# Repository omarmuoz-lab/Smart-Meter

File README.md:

# Smart Meter – Firmware & PCB Designs

This repository contains all the resources for a custom-built **Smart Meter**, including:

- **Firmware** for the embedded microcontroller.
- **PCB designs** for the hardware implementation.

The project is aimed at real-time measurement of electrical parameters such as voltage, current, active power, reactive power, apparent power, power factor, and energy consumption.

---

## 📂 Repository Structure

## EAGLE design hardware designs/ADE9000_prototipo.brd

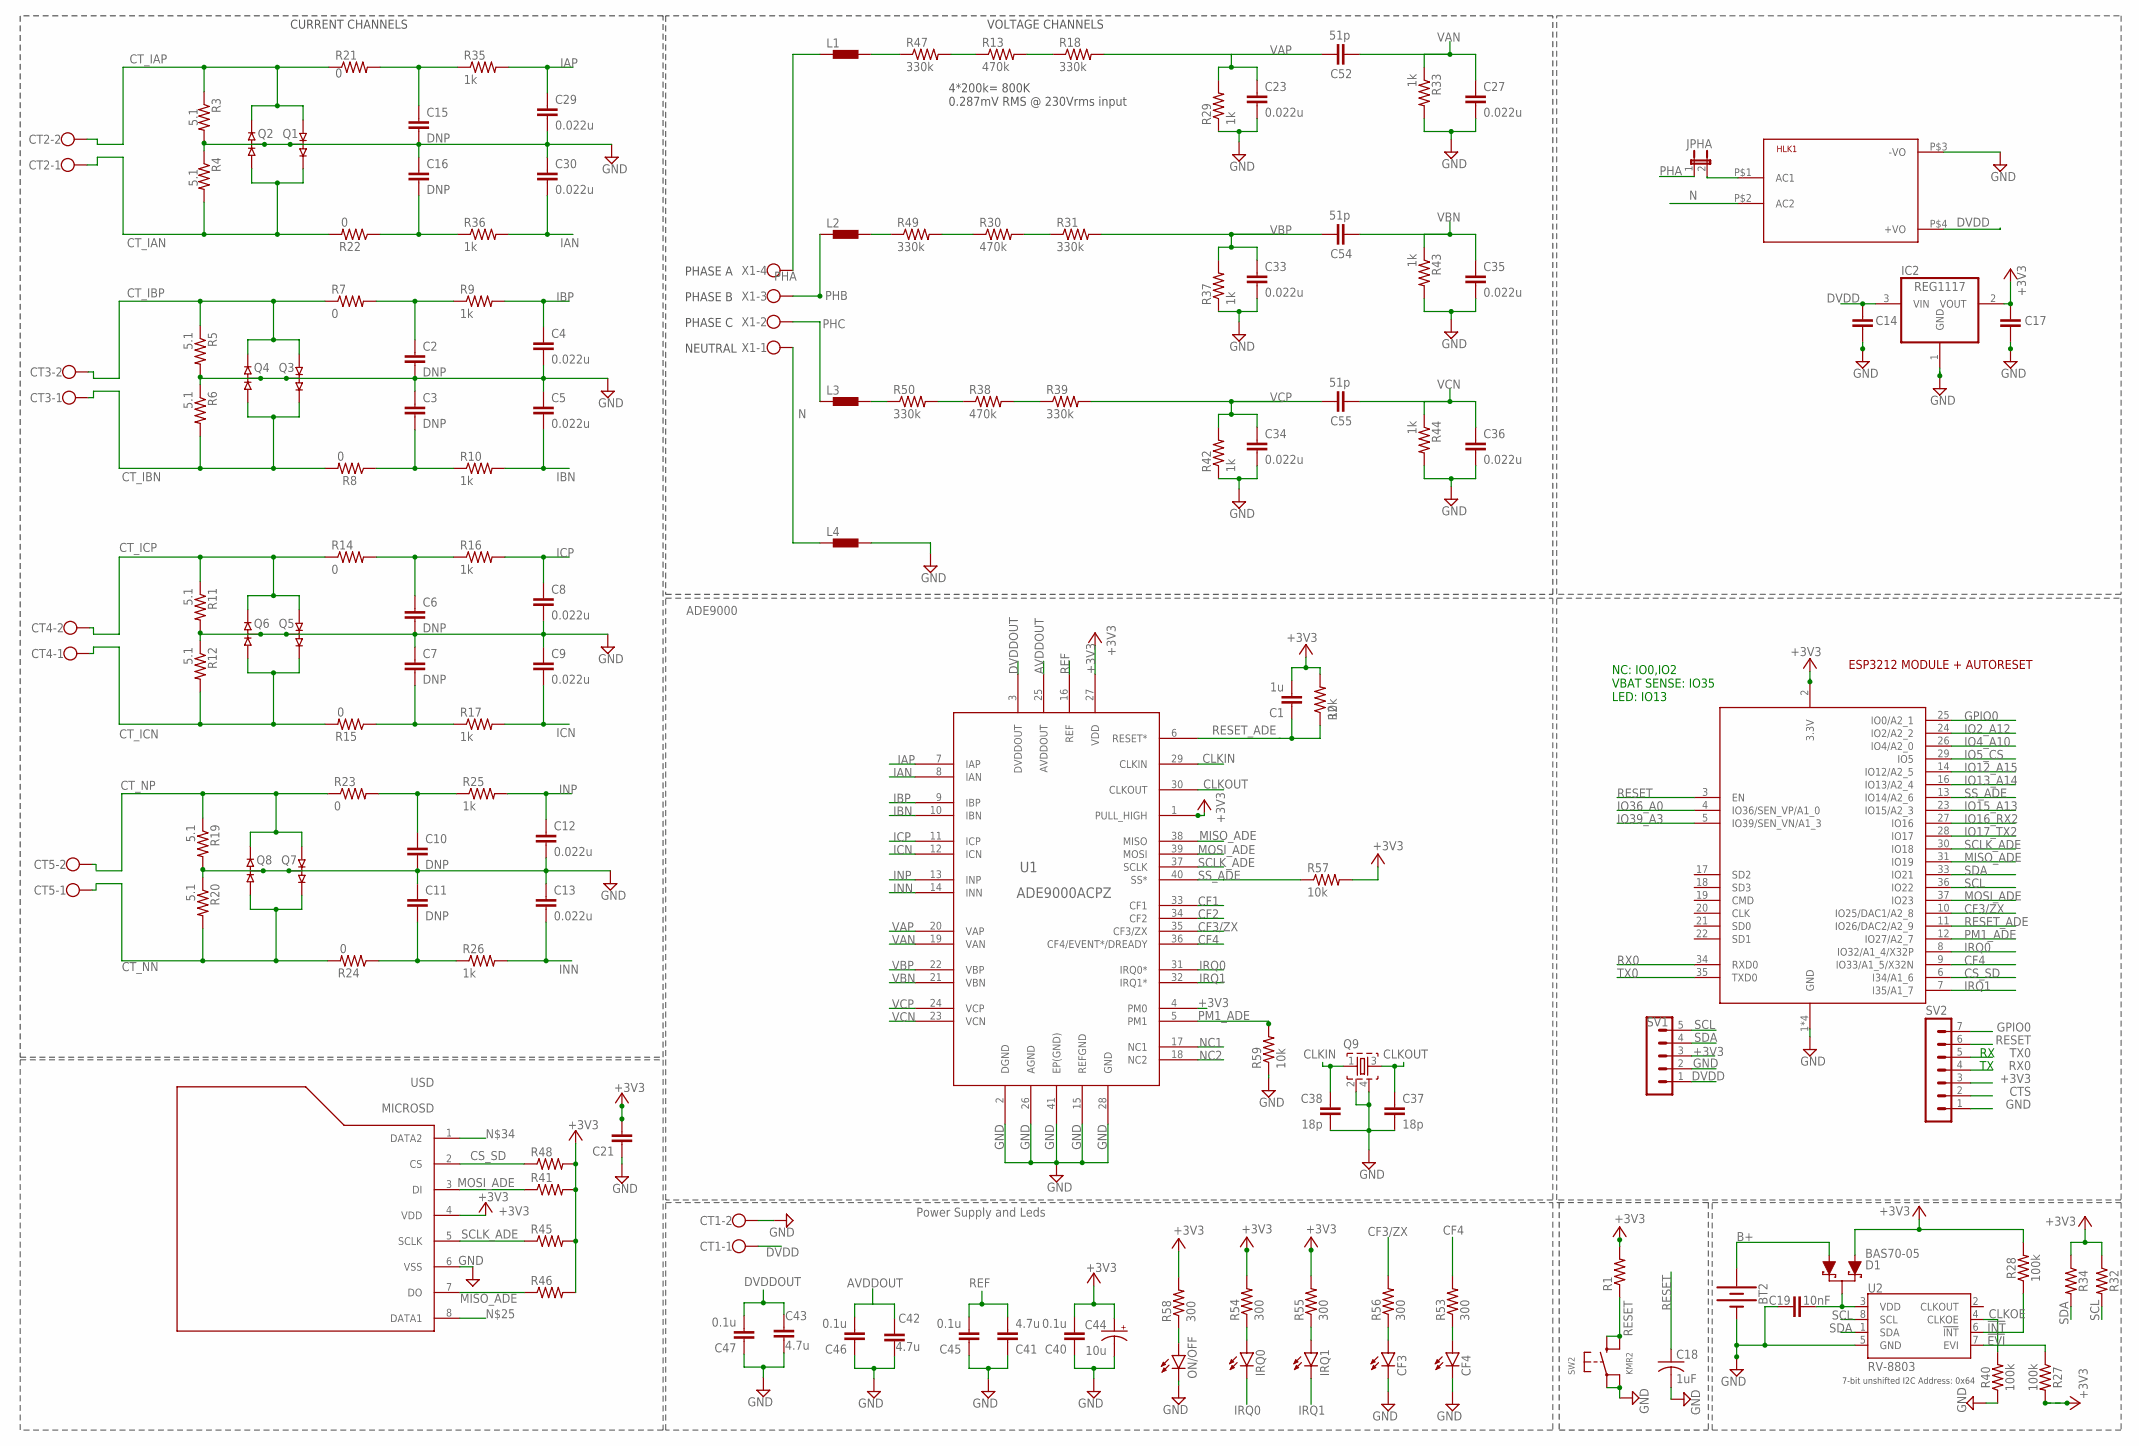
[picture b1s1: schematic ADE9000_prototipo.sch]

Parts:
BT2: BATTERY-12MM_SMD; BATTCON_12MM
C1: 1u; C0805
C2, C3, C6, C7, C10, C11, C15, C16: DNP; C0805
C4, C5, C8, C9, C12, C13, C23, C29, C30, C33, C34: 0.022u; C0805
C14, C17: C-EUC1206; C1206
C18: 1uF; C0805
C19: 10nF; 0603
C21, C40, C45, C46, C47: 0.1u; C0805
C27, C35, C36: 0.022u; C0603
C37, C38: 18p; C0805
C41, C42, C43: 4.7u; C0805
C44: 10u; E1,8-4
C52, C54, C55: 51p; C0603
CF3, CF4: LEDCHIPLED_1206; CHIPLED_1206
CT1, CT2, CT3, CT4, CT5: W237-102
D1: BAS70-05; SOT23-3
HLK1: HLK-PM013W; HLK-PM01
IC2: REG1117; SOT223
IRQ0, IRQ1: LEDCHIPLED_1206; CHIPLED_1206
JPHA: JP1E; JP1
L1, L2, L3, L4: 1500; M0805; DIGIKEY 490-1048-1-ND
ON/OFF: LEDCHIPLED_1206; CHIPLED_1206
Q1, Q2, Q3, Q4, Q5, Q6, Q7, Q8: MMBD4148SE; SOT23-3; DIGIKEY MMBD4148SECT-ND
Q9: ECS-245.7-12-33Q-JES-TR; SMD_4PIN_3.2X2.1; DIGIKEY XC2178CT-ND
R1, R41, R45, R46, R48: R-US_R0805; R0805
R2, R57, R59: 10k; R0805
R3, R5, R11, R19: 5.1; R0805; MFR_PART_NO_# CPF0805B5R1E1
R4, R6, R12, R20: 5.1; R0805
R7, R8, R14, R15, R21, R22, R23, R24: 0; R0805
R9, R10, R16, R17, R25, R26, R29, R35, R36, R37, R42: 1k; R0805
R13, R30, R38: 470k; R0805
R18, R31, R39, R47, R49, R50: 330k; R0805
R27, R28, R40: 100k; 0603
R32: 4.7k; 0603
R33, R43, R44: 1k; R0603
R34: 4.7KOHM-0603-1/10W-1%; 0603
R53, R54, R55, R56, R58: 300; R0805
SV1: MA05-1
SV2: MA07-1
SW2: KMR2; BTN_KMR2_4.6X2.8
U1: ADE9000ACPZ; CP_40_7; DIGIKEY ADE9000ACPZ-RLCT-ND
U2: RV-8803; RV-3028
USD: MICROSD
X1: W237-4
X4: ESP32_WROOM32_SKINNY; WROOM32_SKINNY

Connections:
!EVI: R27.1, U2.7 (EVI)
!INT: R28.1, U2.6 (!INT)
+3V3: C1.2, C17.1, C21.2, C40.2, C44.+, D1.1 (A), IC2.2 (VOUT), R1.2, R2.2, R27.2, R28.2, R32.1, R34.1, R41.2, R45.2, R46.2, R48.2, R54.2, R55.2, R57.2, R58.2, SV1.3, SV2.3, U1.1 (PULL_HIGH), U1.4 (PM0), U1.27 (VDD), USD.4 (VDD), X4.2 (3.3V)
AVDDOUT: C42.1, C46.2, U1.25 (AVDDOUT)
B+: BT2.PWR@1 (+), D1.2 (A1)
CF1: U1.33 (CF1)
CF2: U1.34 (CF2)
CF3/ZX: R56.2, U1.35 (CF3/ZX), X4.10 (IO25/DAC1/A2_8)
CF4: R53.2, U1.36 (CF4/EVENT*/DREADY), X4.9 (IO33/A1_5/X32N)
CLKIN: C38.1, Q9.1, U1.29 (CLKIN)
CLKOE: R40.2, U2.4 (CLKOE)
CLKOUT: C37.1, Q9.3, U1.30 (CLKOUT)
CS_SD: R48.1, USD.2 (CS), X4.6 (I34/A1_6)
CTS: SV2.2
CT_IAN: CT2.1, Q1.2, Q2.1, R4.2, R22.2
CT_IAP: CT2.2, Q1.1, Q2.2, R3.1, R21.1
CT_IBN: CT3.1, Q3.2, Q4.1, R6.2, R8.2
CT_IBP: CT3.2, Q3.1, Q4.2, R5.1, R7.1
CT_ICN: CT4.1, Q5.2, Q6.1, R12.2, R15.2
CT_ICP: CT4.2, Q5.1, Q6.2, R11.1, R14.1
CT_NN: CT5.1, Q7.2, Q8.1, R20.2, R24.2
CT_NP: CT5.2, Q7.1, Q8.2, R19.1, R23.1
DVDD: C14.1, CT1.1, HLK1.P$4 (+VO), IC2.3 (VIN), SV1.1
DVDDOUT: C43.1, C47.2, U1.3 (DVDDOUT)
GND: BT2.GND (-), C2.2, C3.1, C4.2, C5.1, C6.2, C7.1, C8.2, C9.1, C10.2, C11.1, C12.2, C13.1, C14.2, C15.2, C16.1, C17.2, C18.2, C19.1, C21.1, C23.2, C27.2, C29.2, C30.1, C33.2, C34.2, C35.2, C36.2, C37.2, C38.2, C40.1, C41.1, C42.2, C43.2, C44.-, C45.1, C46.1, C47.1, CF3.C, CF4.C, CT1.2, HLK1.P$3 (-VO), IC2.1 (GND), L4.2, ON/OFF.C, Q1.3, Q2.3, Q3.3, Q4.3, Q5.3, Q6.3, Q7.3, Q8.3, Q9.2, Q9.4, R3.2, R4.1, R5.2, R6.1, R11.2, R12.1, R19.2, R20.1, R29.1, R33.2, R37.1, R40.1, R42.1, R43.2, R44.2, R59.1, SV1.2, SV2.1, SW2.A, SW2.A' (P1), U1.2 (DGND), U1.15 (REFGND), U1.26 (AGND), U1.28 (GND), U1.41 (EP(GND)), U2.5 (GND), USD.6 (VSS), X4.1 (GND), X4.15 (GND), X4.38 (GND), X4.P$1 (GND)
GPIO0: SV2.7, X4.25 (IO0/A2_1)
IAN: C30.2, R36.2, U1.8 (IAN)
IAP: C29.1, R35.2, U1.7 (IAP)
IBN: C5.2, R10.2, U1.10 (IBN)
IBP: C4.1, R9.2, U1.9 (IBP)
ICN: C9.2, R17.2, U1.12 (ICN)
ICP: C8.1, R16.2, U1.11 (ICP)
INN: C13.2, R26.2, U1.14 (INN)
INP: C12.1, R25.2, U1.13 (INP)
IO2_A12: X4.24 (IO2/A2_2)
IO4_A10: X4.26 (IO4/A2_0)
IO5_CS: X4.29 (IO5)
IO12_A15: X4.14 (IO12/A2_5)
IO13_A14: X4.16 (IO13/A2_4)
IO15_A13: X4.23 (IO15/A2_3)
IO16_RX2: X4.27 (IO16)
IO17_TX2: X4.28 (IO17)
IO36_A0: X4.4 (IO36/SEN_VP/A1_0)
IO39_A3: X4.5 (IO39/SEN_VN/A1_3)
IRQ0: IRQ0.C, U1.31 (IRQ0*), X4.8 (IO32/A1_4/X32P)
IRQ1: IRQ1.C, U1.32 (IRQ1*), X4.7 (I35/A1_7)
MISO_ADE: R46.1, U1.38 (MISO), USD.7 (DO), X4.31 (IO19)
MOSI_ADE: R41.1, U1.39 (MOSI), USD.3 (DI), X4.37 (IO23)
N: HLK1.P$2 (AC2), L4.1, X1.1
unnamed: C19.2, D1.3 (C), U2.3 (VDD)
unnamed: R13.1, R47.2
unnamed: C3.2, R8.1, R10.1
unnamed: C2.1, R7.2, R9.1
unnamed: HLK1.P$1 (AC1), JPHA.2
unnamed: L3.2, R50.1
unnamed: L2.2, R49.1
unnamed: C7.2, R15.1, R17.1
unnamed: C6.1, R14.2, R16.1
unnamed: C16.2, R22.1, R36.1
unnamed: C11.2, R24.1, R26.1
unnamed: C10.1, R23.2, R25.1
unnamed: CF3.A, R56.1
unnamed: ON/OFF.A, R58.1
unnamed: IRQ0.A, R54.1
unnamed: IRQ1.A, R55.1
unnamed: CF4.A, R53.1
unnamed: R30.1, R49.2
unnamed: R30.2, R31.1
unnamed: L1.2, R47.1
unnamed: R13.2, R18.1
unnamed: C15.1, R21.2, R35.1
unnamed: R38.1, R50.2
unnamed: R38.2, R39.1
NC1: U1.17 (NC1)
NC2: U1.18 (NC2)
PHA: JPHA.1, L1.1, X1.4
PHB: L2.1, X1.3
PHC: L3.1, X1.2
PM1_ADE: R59.2, U1.5 (PM1), X4.12 (IO27/A2_7)
REF: C41.2, C45.2, U1.16 (REF)
RESET: C18.1, R1.1, SV2.6, SW2.B (S), SW2.B' (S1), X4.3 (EN)
RESET_ADE: C1.1, R2.1, U1.6 (RESET*), X4.11 (IO26/DAC2/A2_9)
RX0: SV2.4, X4.34 (RXD0)
SCL: R32.2, SV1.5, U2.8 (SCL), X4.36 (IO22)
SCLK_ADE: R45.1, U1.37 (SCLK), USD.5 (SCLK), X4.30 (IO18)
SDA: R34.2, SV1.4, U2.1 (SDA), X4.33 (IO21)
SS_ADE: R57.1, U1.40 (SS*), X4.13 (IO14/A2_6)
TX0: SV2.5, X4.35 (TXD0)
VAN: C27.1, C52.1, R33.1, U1.19 (VAN)
VAP: C23.1, C52.2, R18.2, R29.2, U1.20 (VAP)
VBN: C35.1, C54.1, R43.1, U1.21 (VBN)
VBP: C33.1, C54.2, R31.2, R37.2, U1.22 (VBP)
VCN: C36.1, C55.1, R44.1, U1.23 (VCN)
VCP: C34.1, C55.2, R39.2, R42.2, U1.24 (VCP)

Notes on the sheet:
CURRENT CHANNELS
VOLTAGE CHANNELS
4*200k= 800K 0.287mV RMS @ 230Vrms input
PHASE A
PHASE B
PHASE C
NEUTRAL
ADE9000
Power Supply and Leds
ESP3212 MODULE + AUTORESET
NC: IO0,IO2 VBAT SENSE: IO35 LED: IO13
7-bit unshifted I2C Address: 0x64

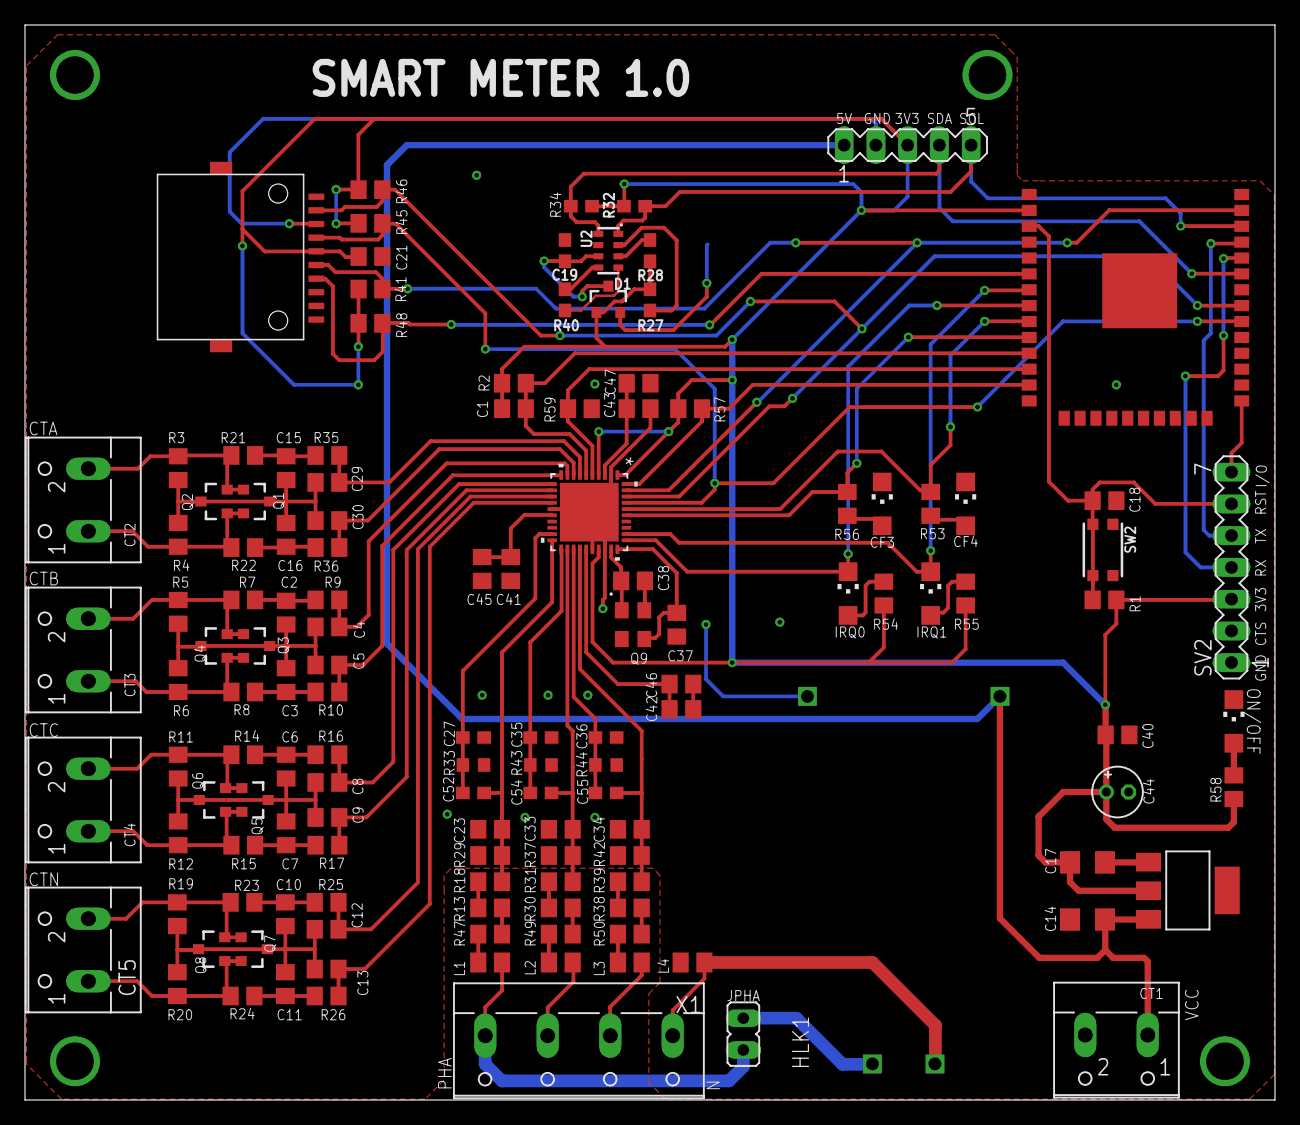
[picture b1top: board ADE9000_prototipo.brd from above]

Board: 2 copper layers, 100.0 x 86.0 mm, 134 parts (1 on the bottom side), 79 nets.

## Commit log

2025-08-11 README.md
2025-08-11 hardware_designs
2025-08-11 Firmware

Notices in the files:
parts and their libraries:
microbuilder: This work is placed in the public domain, and may be freely used for commercial and non-commercial work with the following conditions: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
SparkFun-Clocks: Licensing: Creative Commons ShareAlike 4.0 International - https://creativecommons.org/licenses/by-sa/4.0
